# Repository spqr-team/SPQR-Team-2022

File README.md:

# SPQR-Team-2022
SPQR team soccer repo

Soccer lightweight SPQR team

On the road for Bangkok

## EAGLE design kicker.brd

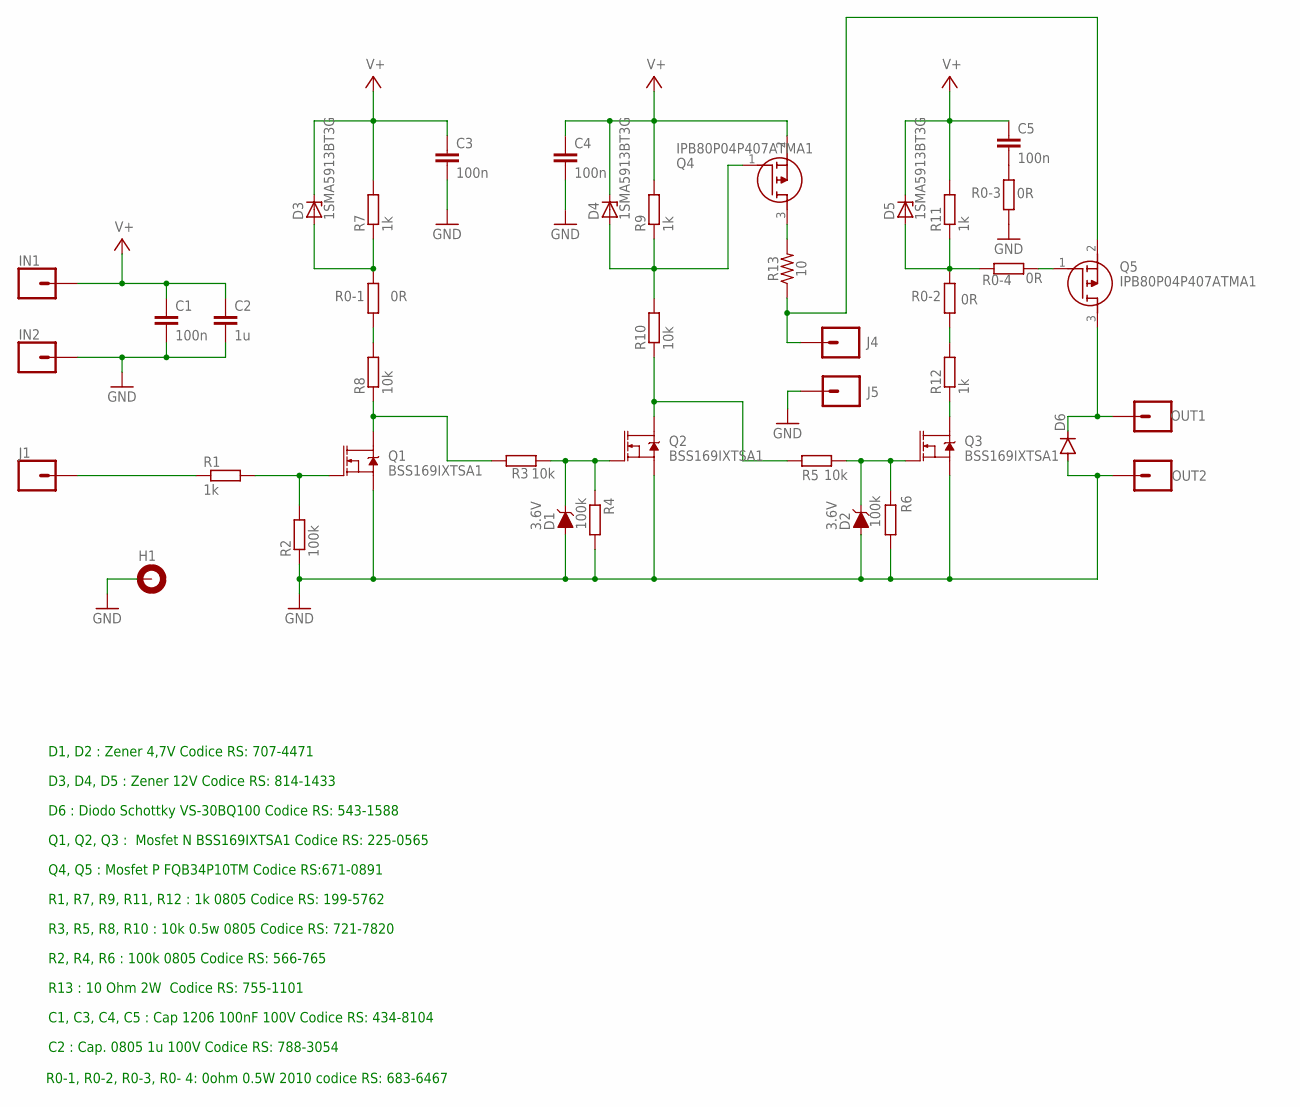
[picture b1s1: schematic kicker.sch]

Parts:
C1, C3, C4, C5: 100n; C1206
C2: 1u; C1206
D1, D2: 3.6V; SOD-323
D3, D4, D5: 1SMA5913BT3G; DO214AC
D6: DIODE-SMC; SMC
H1: MOUNT-PAD-ROUND3.0; 3,0-PAD
IN1, IN2: CONN_01; 1X01
J1, J4, J5: CONN_01; 1X01
OUT1, OUT2: CONN_01; 1X01
Q1, Q2, Q3: BSS169IXTSA1; SOT23-3
Q4, Q5: IPB80P04P407ATMA1; PG-TO263-3-2_1
R0-1, R0-2, R0-3, R0-4: 0R; R2010
R1, R7, R9, R11, R12: 1k; R1206
R2, R4, R6: 100k; R1206
R3, R5, R8, R10: 10k; R1206
R13: 10; 1210

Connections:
GND: C1.2, C2.2, C3.2, C4.2, D1.A, D2.A, D6.A, H1.B3,0, IN2.1, J5.1, OUT2.1, Q1.2 (S), Q2.2 (S), Q3.2 (S), R0-3.1, R2.1, R4.2, R6.1
unnamed: J1.1, R1.1
unnamed: Q1.1 (G), R1.2, R2.2
unnamed: D1.C, Q2.1 (G), R3.1, R4.1
unnamed: D2.C, Q3.1 (G), R5.2, R6.2
unnamed: Q1.3 (D), R3.2, R8.1
unnamed: R0-1.1, R8.2
unnamed: Q2.3 (D), R5.1, R10.1
unnamed: D4.A, Q4.1 (G), R9.1, R10.2
unnamed: Q4.3 (D), R13.2
unnamed: D3.A, R0-1.2, R7.1
unnamed: D6.C, OUT1.1, Q5.3 (D)
unnamed: J4.1, Q5.2 (S), R13.1
unnamed: R0-2.1, R12.2
unnamed: C5.2, R0-3.2
unnamed: D5.A, R0-2.2, R0-4.2, R11.1
unnamed: Q3.3 (D), R12.1
unnamed: Q5.1 (G), R0-4.1
V+: C1.1, C2.1, C3.1, C4.1, C5.1, D3.C, D4.C, D5.C, IN1.1, Q4.2 (S), R7.2, R9.2, R11.2

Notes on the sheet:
D1, D2 : Zener 4,7V Codice RS: 707-4471
D3, D4, D5 : Zener 12V Codice RS: 814-1433
R13 : 10 Ohm 2W Codice RS: 755-1101
D6 : Diodo Schottky VS-30BQ100 Codice RS: 543-1588
Q1, Q2, Q3 : Mosfet N BSS169IXTSA1 Codice RS: 225-0565
Q4, Q5 : Mosfet P FQB34P10TM Codice RS:671-0891
R1, R7, R9, R11, R12 : 1k 0805 Codice RS: 199-5762
R3, R5, R8, R10 : 10k 0.5w 0805 Codice RS: 721-7820
R2, R4, R6 : 100k 0805 Codice RS: 566-765
C1, C3, C4, C5 : Cap 1206 100nF 100V Codice RS: 434-8104
C2 : Cap. 0805 1u 100V Codice RS: 788-3054
R0-1, R0-2, R0-3, R0- 4: 0ohm 0.5W 2010 codice RS: 683-6467

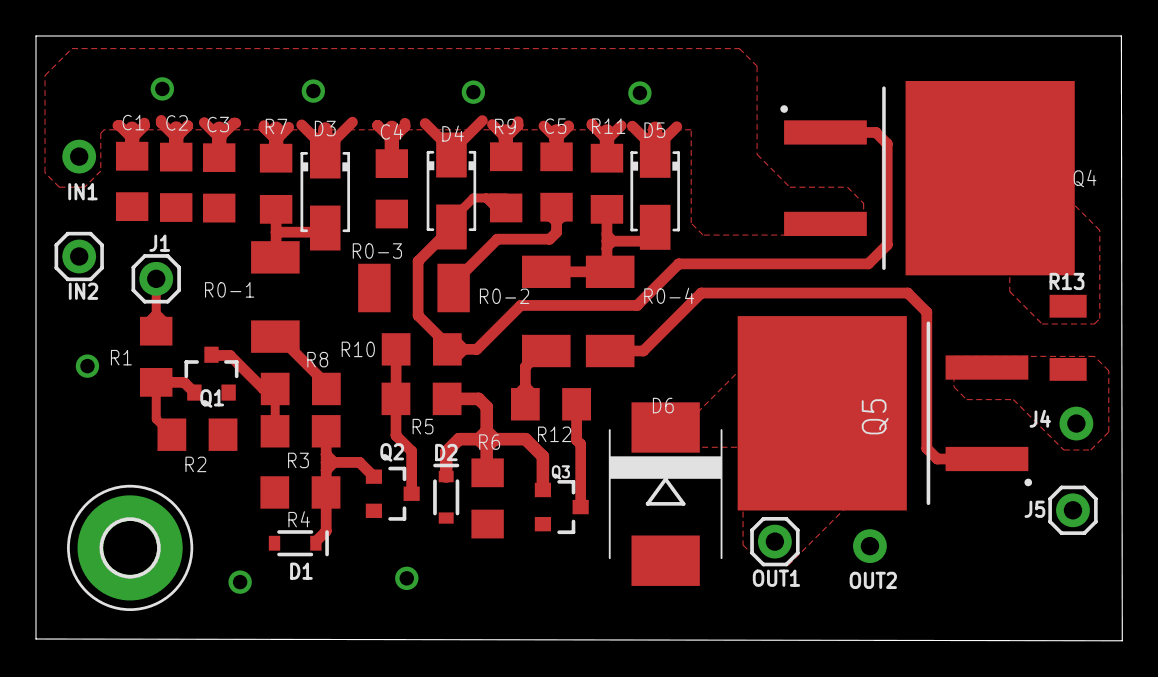
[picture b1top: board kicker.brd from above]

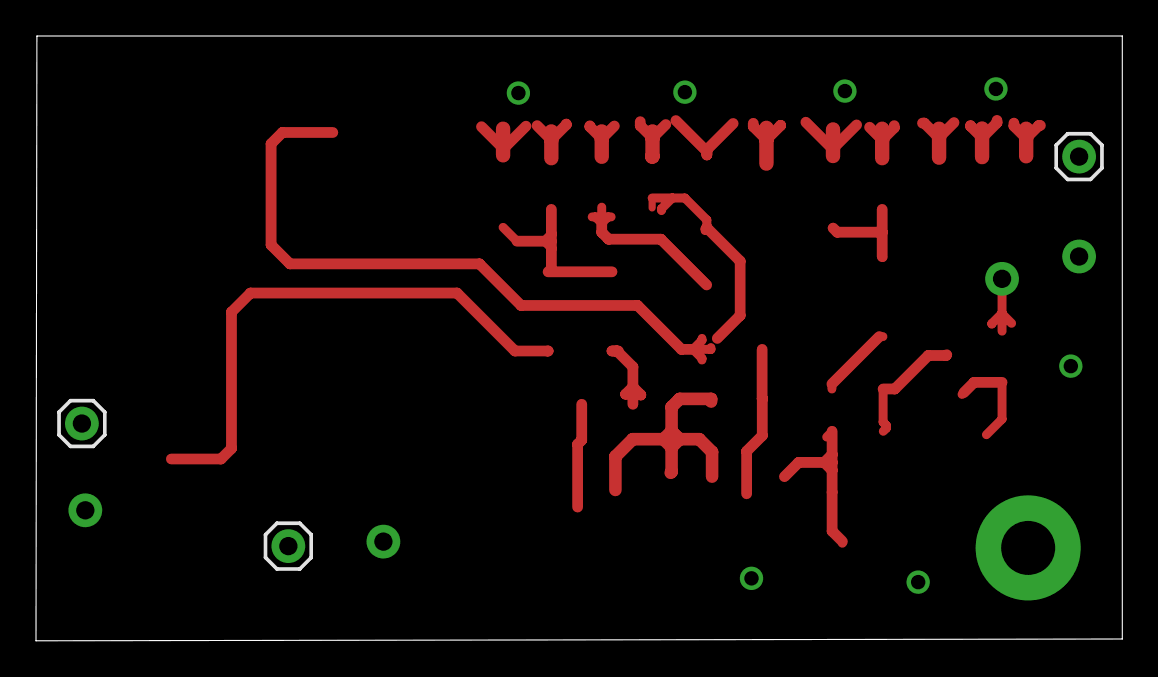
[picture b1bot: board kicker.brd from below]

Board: 2 copper layers, 60.4 x 33.6 mm, 41 parts (3 on the bottom side), 19 nets.

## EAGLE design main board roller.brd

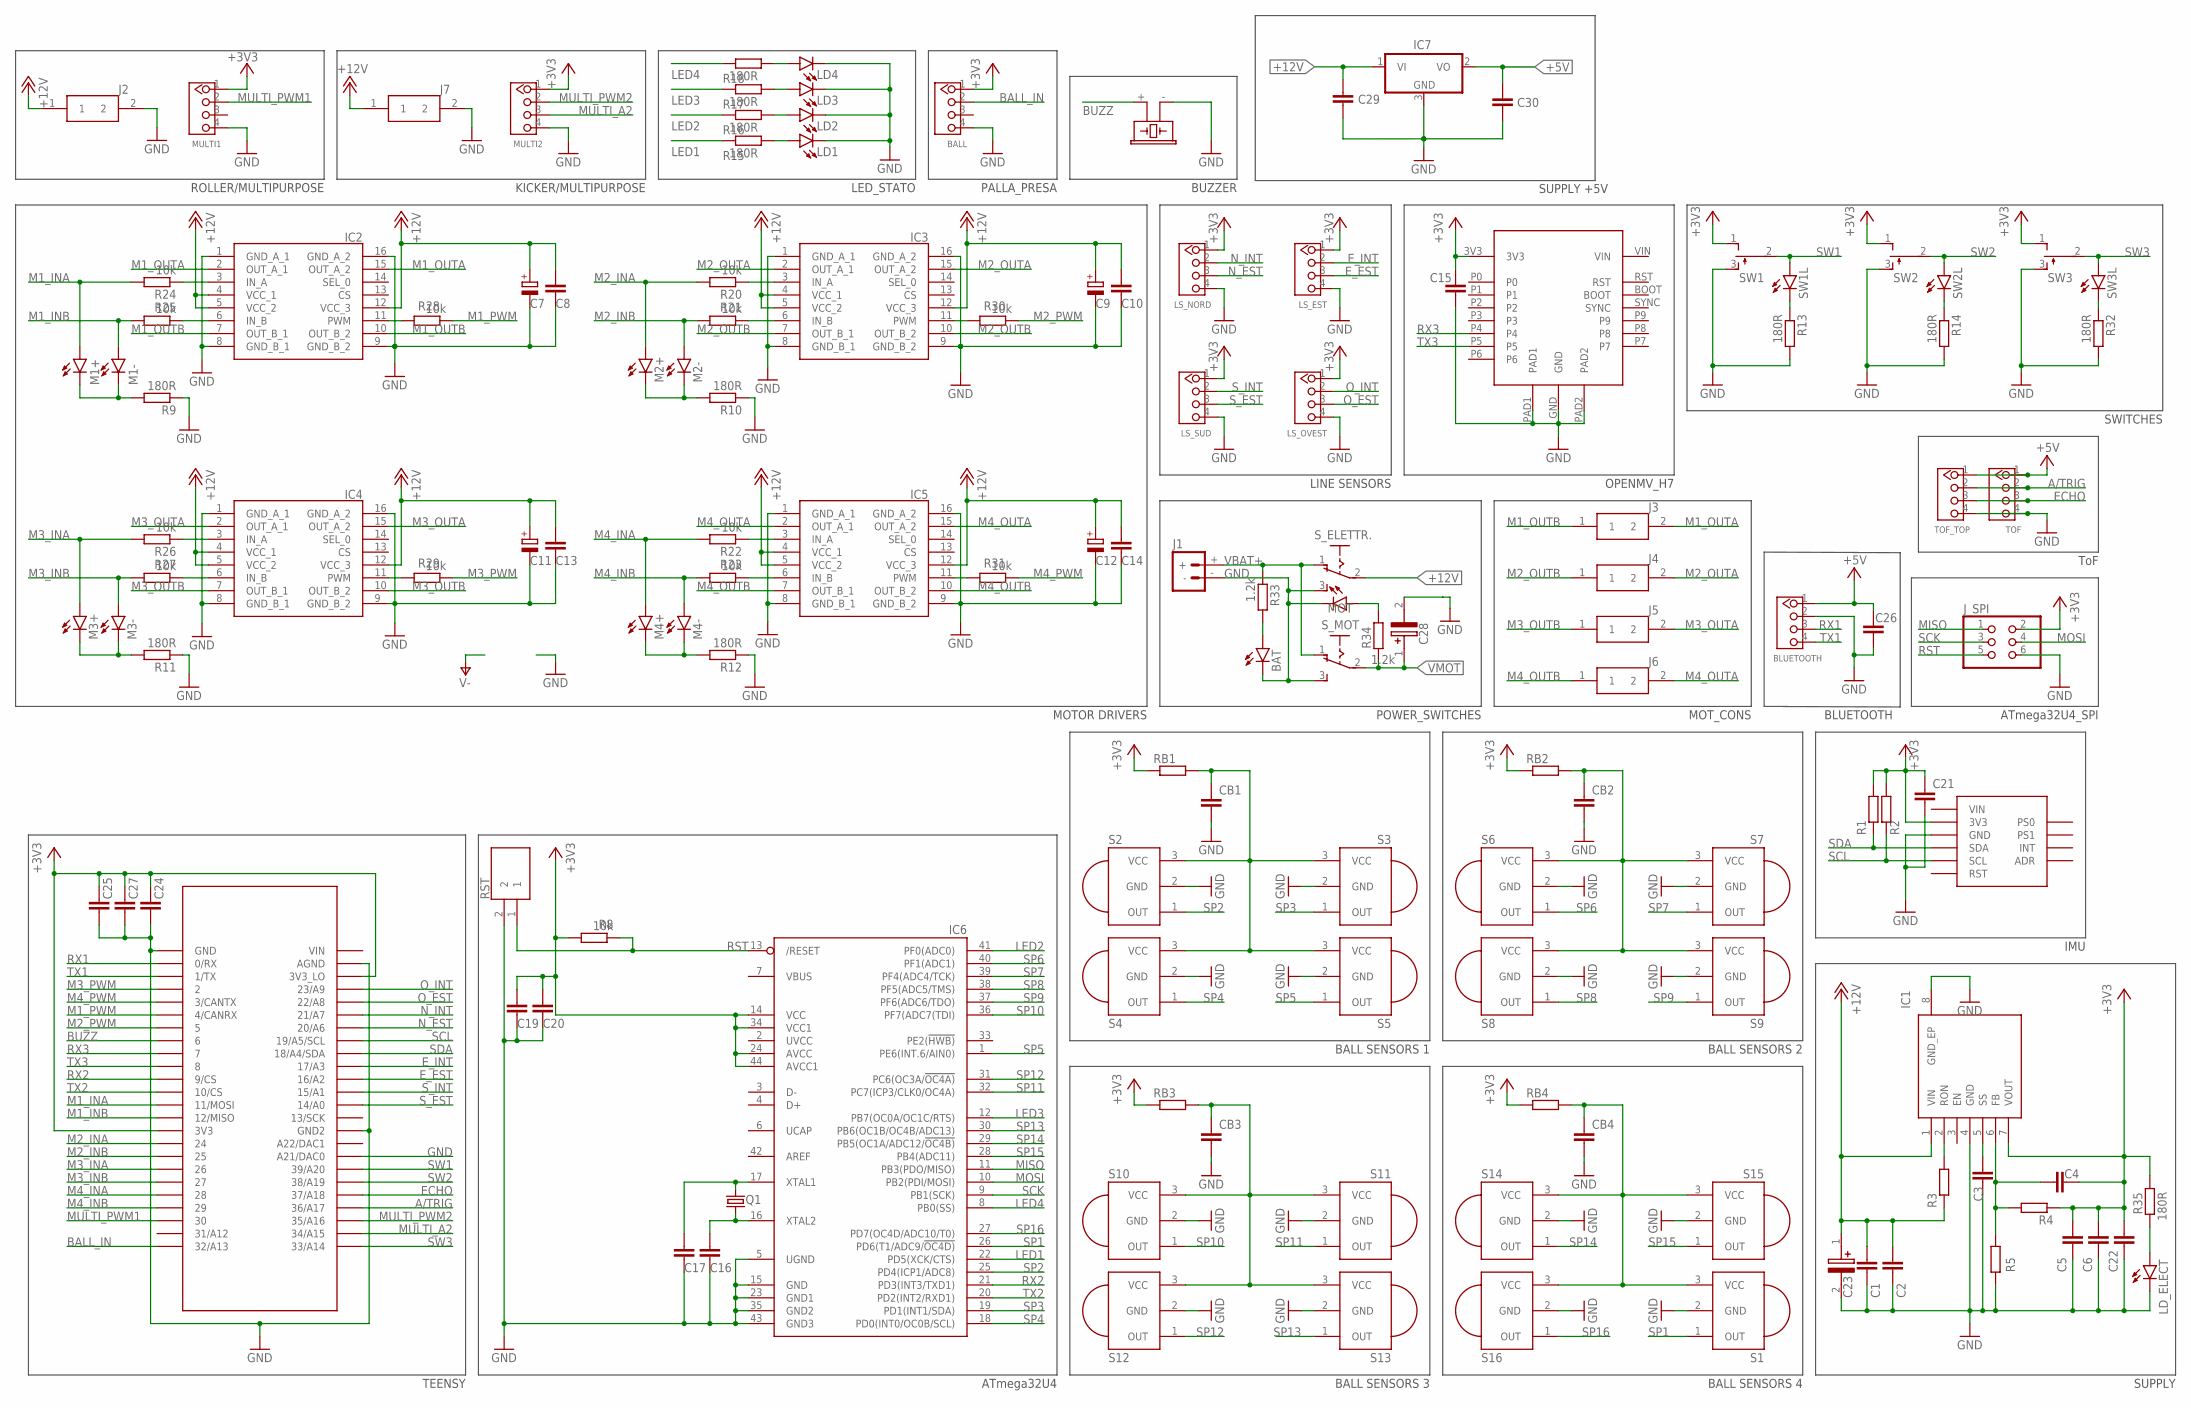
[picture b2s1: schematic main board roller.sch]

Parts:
BALL: TWIG_2.0; 2.0_1X4
BAT: LEDCHIPLED_1206; CHIPLED_1206
BLUETOOTH: TWIG_2.0; 2.0_1X4
BUZZER: F/CM12P
C1, C2, C22, C24, C27: 100n; C0805
C3, C4: 22n; C0805
C5, C6: 100u; C1206
C7: 1OOu; PANASONIC_E
C8, C10, C13, C14, C15, C20, C21, C26: 1u; C0805
C9, C11, C12: 100u; PANASONIC_E
C16, C17: 22pF; C0805
C19: 1u; C1206
C23, C28: EEV-FK1C152Q; FKV(H13)
C25: 100n; C1206
C29, C30: 1uF; C0805
CB1, CB2, CB3, CB4: 0.1uF; C0805
IC1: LMZ14202TZE-ADJ_NOPB; NDW0007A
IC2, IC3, IC4, IC5: VNH7070ASTR; SOIC127P600X175-16N
IC6: ATMEGA32U4-AU; TQFP44
IC7: 7805DT; TO252
J1: BATTERY_CONN_DEANS; DEANS
J2, J3, J4, J5, J6, J7: 43650-0201; 43650-0200
J_SPI: PINHD-2X3; 2X03
LD1, LD2, LD3, LD4: LEDCHIPLED_1206; CHIPLED_1206
LD_ELECT: LEDCHIPLED_1206; CHIPLED_1206
LS_EST: TWIG_2.0; 2.0_1X4
LS_NORD: TWIG_2.0; 2.0_1X4
LS_OVEST: TWIG_2.0; 2.0_1X4
LS_SUD: TWIG_2.0; 2.0_1X4
M1+, M1-, M2+, M2-, M3+, M3-, M4+, M4-: LEDCHIPLED_1206; CHIPLED_1206
MOT: LEDCHIPLED_1206; CHIPLED_1206
MULTI1, MULTI2: TWIG_2.0; 2.0_1X4
Q1: CRYSTALHC49UP; HC49UP
R1, R2, R8, R20, R21, R22, R23, R24, R25, R26, R27, R28, R29, R30, R31: 10k; R0805
R3: 61,9k; R0805
R4: 3,32k; R0805
R5: 1,07k; R0805
R9, R10, R11, R12, R13, R14, R15, R16, R17, R18, R32, R35: 180R; R0805
R33, R34: 1.2k; R0805
RB1, RB2, RB3, RB4: 22; R0805
RST: KSR231GLFS; KSR
S1, S2, S3, S4, S5, S6, S7, S8, S9, S10, S11, S12, S13, S14, S15, S16: PNA460XM
SW1, SW2, SW3: TL38PO; TL3XPO
SW1L, SW2L, SW3L: LEDCHIPLED_1206; CHIPLED_1206
S_ELETTR.: 255SB
S_MOT: 255SB
TOF: TWIG_2.0; 2.0_1X4
TOF_TOP: TWIG_2.0; 2.0_1X4
U$1: TEENSY_3.5/3.6
U$2: OPENMV_H7
U$4: BNO055

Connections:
+3V3: BALL.1, C4.2, C5.1, C6.1, C15.1, C19.1, C20.1, C21.1, C22.1, C24.1, C25.1, C27.1, IC1.7 (VOUT), IC6.14 (VCC), IC6.24 (AVCC), IC6.34 (VCC1), IC6.44 (AVCC1), J_SPI.2, LS_EST.1, LS_NORD.1, LS_OVEST.1, LS_SUD.1, MULTI1.1, MULTI2.1, R1.2, R2.2, R4.1, R8.2, R35.2, RB1.1, RB2.1, RB3.1, RB4.1, SW1.1 (O), SW2.1 (O), SW3.1 (O), U$1.3V3, U$1.3V3_LO, U$2.3V3, U$4.3V3
+5V: BLUETOOTH.1, C26.1, C30.1, IC7.2 (VO), TOF.1, TOF_TOP.1
+12V: C1.1, C2.1, C23.1 (+), C29.1, IC1.1 (VIN), IC7.1 (VI), J2.1, J7.1, R3.1, S_ELETTR..2
A/TRIG: TOF.2, TOF_TOP.2, U$1.36/A17
BALL_IN: BALL.2, U$1.32/A13
BUZZ: BUZZER.+ (1), U$1.6
ECHO: TOF.3, TOF_TOP.3, U$1.37/A18
E_EST: LS_EST.3, U$1.16/A2
E_INT: LS_EST.2, U$1.17/A3
GND: BALL.4, BAT.C, BLUETOOTH.2, BUZZER.- (2), C1.2, C2.2, C3.2, C5.2, C6.2, C7.-, C8.2, C9.-, C10.2, C11.-, C12.-, C13.2, C14.2, C15.2, C16.2, C17.2, C19.2, C20.2, C21.2, C22.2, C23.2 (-), C24.2, C25.2, C26.2, C27.2, C28.2 (-), C29.2, C30.2, CB1.2, CB2.2, CB3.2, CB4.2, IC1.4 (GND), IC1.8 (GND_EP), IC2.1 (GND_A_1), IC2.8 (GND_B_1), IC2.9 (GND_B_2), IC2.16 (GND_A_2), IC3.1 (GND_A_1), IC3.8 (GND_B_1), IC3.9 (GND_B_2), IC3.16 (GND_A_2), IC4.1 (GND_A_1), IC4.8 (GND_B_1), IC4.9 (GND_B_2), IC4.16 (GND_A_2), IC5.1 (GND_A_1), IC5.8 (GND_B_1), IC5.9 (GND_B_2), IC5.16 (GND_A_2), IC6.5 (UGND), IC6.15 (GND), IC6.23 (GND1), IC6.35 (GND2), IC6.43 (GND3), IC7.3 (GND), J1.-, J2.2, J7.2, J_SPI.6, LD1.C, LD2.C, LD3.C, LD4.C, LD_ELECT.C, LS_EST.4, LS_NORD.4, LS_OVEST.4, LS_SUD.4, MOT.C, MULTI1.4, MULTI2.4, R5.1, R9.1, R10.1, R11.1, R12.1, R13.2, R14.2, R32.2, RST.2, S1.2 (GND), S2.2 (GND), S3.2 (GND), S4.2 (GND), S5.2 (GND), S6.2 (GND), S7.2 (GND), S8.2 (GND), S9.2 (GND), S10.2 (GND), S11.2 (GND), S12.2 (GND), S13.2 (GND), S14.2 (GND), S15.2 (GND), S16.2 (GND), SW1.3 (S), SW2.3 (S), SW3.3 (S), S_ELETTR..3 (S), S_MOT.3 (S), TOF.4, TOF_TOP.4, U$1.21/DAC0 (A21/DAC0), U$1.AGND, U$1.GND, U$1.GND2, U$2.GND, U$2.PAD1, U$2.PAD2, U$4.GND
INA_1: IC2.3 (IN_A), R24.1
INA_2: IC3.3 (IN_A), R20.1
INA_3: IC4.3 (IN_A), R26.1
INA_4: IC5.3 (IN_A), R22.1
INB_1: IC2.6 (IN_B), R25.1
INB_2: IC3.6 (IN_B), R21.1
INB_3: IC4.6 (IN_B), R27.1
INB_4: IC5.6 (IN_B), R23.1
LED1: IC6.22 (PD5(XCK/CTS)), R15.1
LED2: IC6.41 (PF0(ADC0)), R16.1
LED3: IC6.12 (PB7(OC0A/OC1C/RTS)), R17.1
LED4: IC6.8 (PB0(SS)), R18.1
M1_INA: M1+.A, R24.2, U$1.11/MOSI
M1_INB: M1-.A, R25.2, U$1.12/MISO
M1_OUTA: IC2.2 (OUT_A_1), IC2.15 (OUT_A_2), J3.2
M1_OUTB: IC2.7 (OUT_B_1), IC2.10 (OUT_B_2), J3.1
M1_PWM: R28.1, U$1.4/CANRX
M2_INA: M2+.A, R20.2, U$1.24
M2_INB: M2-.A, R21.2, U$1.25
M2_OUTA: IC3.2 (OUT_A_1), IC3.15 (OUT_A_2), J4.2
M2_OUTB: IC3.7 (OUT_B_1), IC3.10 (OUT_B_2), J4.1
M2_PWM: R30.1, U$1.5
M3_INA: M3+.A, R26.2, U$1.26
M3_INB: M3-.A, R27.2, U$1.27
M3_OUTA: IC4.2 (OUT_A_1), IC4.15 (OUT_A_2), J5.2
M3_OUTB: IC4.7 (OUT_B_1), IC4.10 (OUT_B_2), J5.1
M3_PWM: R29.1, U$1.2
M4_INA: M4+.A, R22.2, U$1.28
M4_INB: M4-.A, R23.2, U$1.29
M4_OUTA: IC5.2 (OUT_A_1), IC5.15 (OUT_A_2), J6.2
M4_OUTB: IC5.7 (OUT_B_1), IC5.10 (OUT_B_2), J6.1
M4_PWM: R31.1, U$1.3/CANTX
MISO: IC6.11 (PB3(PDO/MISO)), J_SPI.1
MOSI: IC6.10 (PB2(PDI/MOSI)), J_SPI.4
MULTI_A2: MULTI2.3, U$1.34/A15
MULTI_PWM1: MULTI1.2, U$1.30
MULTI_PWM2: MULTI2.2, U$1.35/A16
unnamed: IC1.2 (RON), R3.2
unnamed: C4.1, IC1.6 (FB), R4.2, R5.2
unnamed: C3.1, IC1.5 (SS)
unnamed: LD4.A, R18.2
unnamed: C17.1, IC6.17 (XTAL1), Q1.2
unnamed: C16.1, IC6.16 (XTAL2), Q1.1
unnamed: M2+.C, M2-.C, R10.2
unnamed: M1+.C, M1-.C, R9.2
unnamed: M3+.C, M3-.C, R11.2
unnamed: M4+.C, M4-.C, R12.2
unnamed: R13.1, SW1L.C
unnamed: R14.1, SW2L.C
unnamed: R32.1, SW3L.C
unnamed: LD1.A, R15.2
unnamed: LD2.A, R16.2
unnamed: LD3.A, R17.2
unnamed: BAT.A, R33.2
unnamed: MOT.A, R34.2
unnamed: LD_ELECT.A, R35.1
N_EST: LS_NORD.3, U$1.20/A6
N_INT: LS_NORD.2, U$1.21/A7
O_EST: LS_OVEST.3, U$1.22/A8
O_INT: LS_OVEST.2, U$1.23/A9
POWER_BLOCK_1: CB1.1, RB1.2, S2.3 (VCC), S3.3 (VCC), S4.3 (VCC), S5.3 (VCC)
POWER_BLOCK_2: CB2.1, RB2.2, S6.3 (VCC), S7.3 (VCC), S8.3 (VCC), S9.3 (VCC)
POWER_BLOCK_3: CB3.1, RB3.2, S10.3 (VCC), S11.3 (VCC), S12.3 (VCC), S13.3 (VCC)
POWER_BLOCK_4: CB4.1, RB4.2, S1.3 (VCC), S14.3 (VCC), S15.3 (VCC), S16.3 (VCC)
PWM3: IC4.11 (PWM), R29.2
PWM_1: IC2.11 (PWM), R28.2
PWM_2: IC3.11 (PWM), R30.2
PWM_4: IC5.11 (PWM), R31.2
RST: IC6.13 (/RESET), J_SPI.5, R8.1, RST.1
RX1: BLUETOOTH.3, U$1.0/RX
RX2: IC6.21 (PD3(INT3/TXD1)), U$1.9/CS
RX3: U$1.7, U$2.P4
SCK: IC6.9 (PB1(SCK)), J_SPI.3
SCL: R2.1, U$1.19/A5/SCL, U$4.SCL
SDA: R1.1, U$1.18/A4/SDA, U$4.SDA
SP1: IC6.26 (PD6(T1/ADC9/!OC4D)), S1.1 (OUT)
SP2: IC6.25 (PD4(ICP1/ADC8)), S2.1 (OUT)
SP3: IC6.19 (PD1(INT1/SDA)), S3.1 (OUT)
SP4: IC6.18 (PD0(INT0/OC0B/SCL)), S4.1 (OUT)
SP5: IC6.1 (PE6(INT.6/AIN0)), S5.1 (OUT)
SP6: IC6.40 (PF1(ADC1)), S6.1 (OUT)
SP7: IC6.39 (PF4(ADC4/TCK)), S7.1 (OUT)
SP8: IC6.38 (PF5(ADC5/TMS)), S8.1 (OUT)
SP9: IC6.37 (PF6(ADC6/TDO)), S9.1 (OUT)
SP10: IC6.36 (PF7(ADC7(TDI)), S10.1 (OUT)
SP11: IC6.32 (PC7(ICP3/CLK0/OC4A)), S11.1 (OUT)
SP12: IC6.31 (PC6(OC3A/!OC4A)), S12.1 (OUT)
SP13: IC6.30 (PB6(OC1B/OC4B/ADC13)), S13.1 (OUT)
SP14: IC6.29 (PB5(OC1A/ADC12/!OC4B)), S14.1 (OUT)
SP15: IC6.28 (PB4(ADC11)), S15.1 (OUT)
SP16: IC6.27 (PD7(OC4D/ADC10/T0)), S16.1 (OUT)
SW1: SW1.2, SW1L.A, U$1.39/A20
SW2: SW2.2, SW2L.A, U$1.38/A19
SW3: SW3.2, SW3L.A, U$1.33/A14
S_EST: LS_SUD.3, U$1.14/A0
S_INT: LS_SUD.2, U$1.15/A1
TX1: BLUETOOTH.4, U$1.1/TX
TX2: IC6.20 (PD2(INT2/RXD1)), U$1.10/CS
TX3: U$1.8, U$2.P5
VBAT+: J1.+, R33.1, S_ELETTR..1 (O), S_MOT.1 (O)
VMOT: C7.+, C8.1, C9.+, C10.1, C11.+, C12.+, C13.1, C14.1, C28.1 (+), IC2.4 (VCC_1), IC2.5 (VCC_2), IC2.12 (VCC_3), IC3.4 (VCC_1), IC3.5 (VCC_2), IC3.12 (VCC_3), IC4.4 (VCC_1), IC4.5 (VCC_2), IC4.12 (VCC_3), IC5.4 (VCC_1), IC5.5 (VCC_2), IC5.12 (VCC_3), R34.1, S_MOT.2

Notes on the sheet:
TEENSY
IMU
SUPPLY
POWER_SWITCHES
BALL SENSORS 1
BALL SENSORS 2
BALL SENSORS 3
BALL SENSORS 4
LINE SENSORS
MOTOR DRIVERS
OPENMV_H7
ATmega32U4
ATmega32U4_SPI
SWITCHES
BUZZER
LED_STATO
MOT_CONS
BLUETOOTH
ToF
ROLLER/MULTIPURPOSE
KICKER/MULTIPURPOSE
PALLA_PRESA
SUPPLY +5V

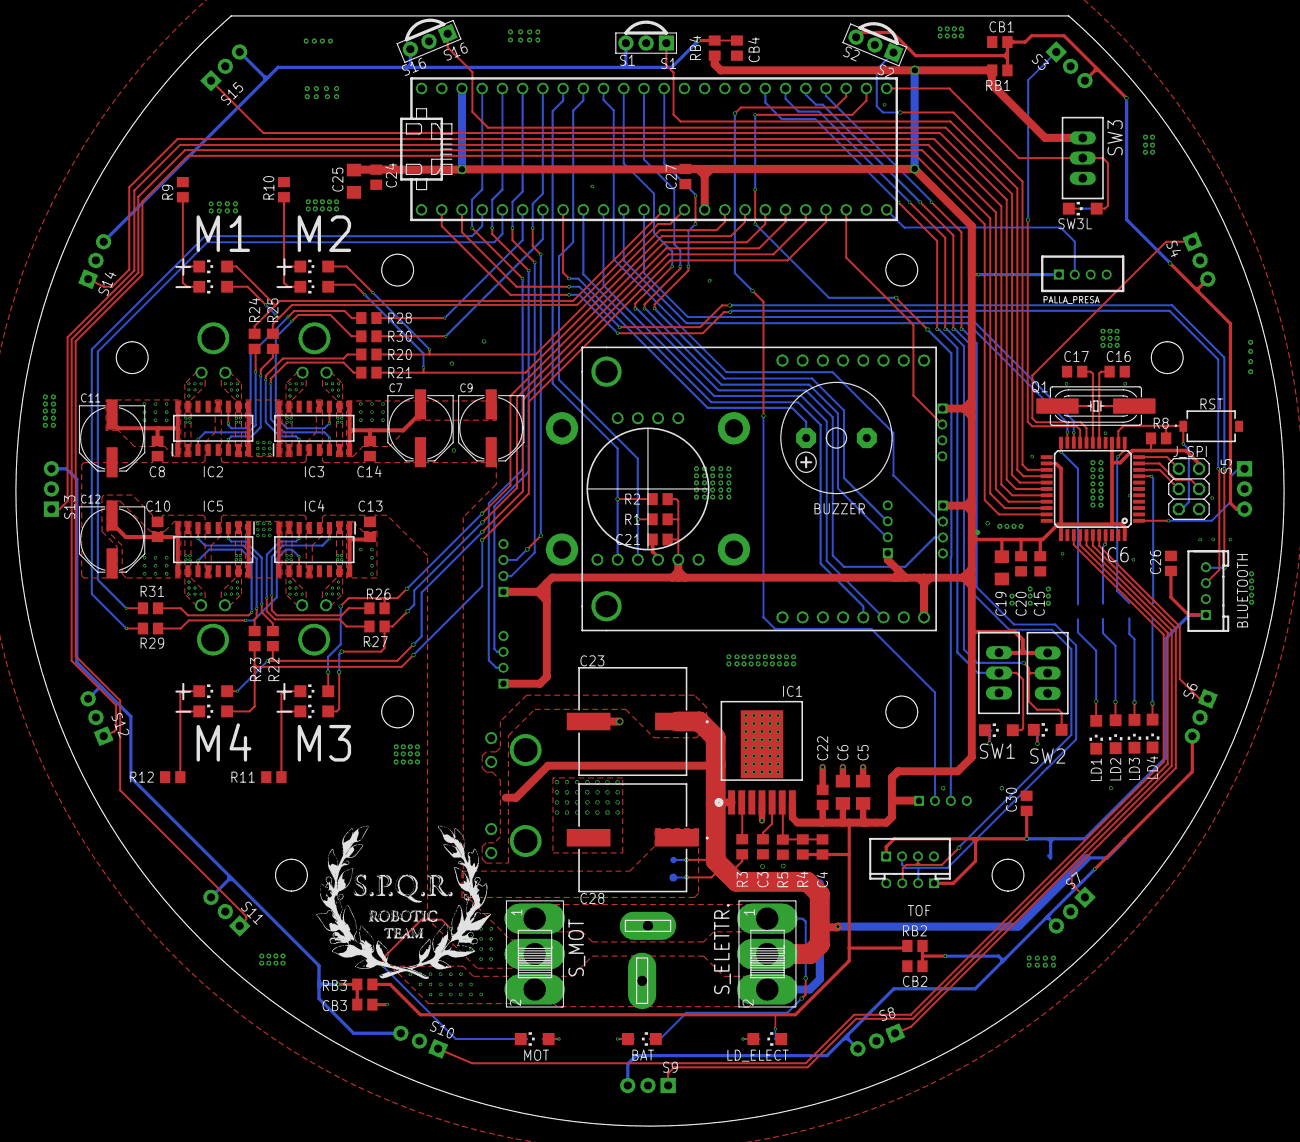
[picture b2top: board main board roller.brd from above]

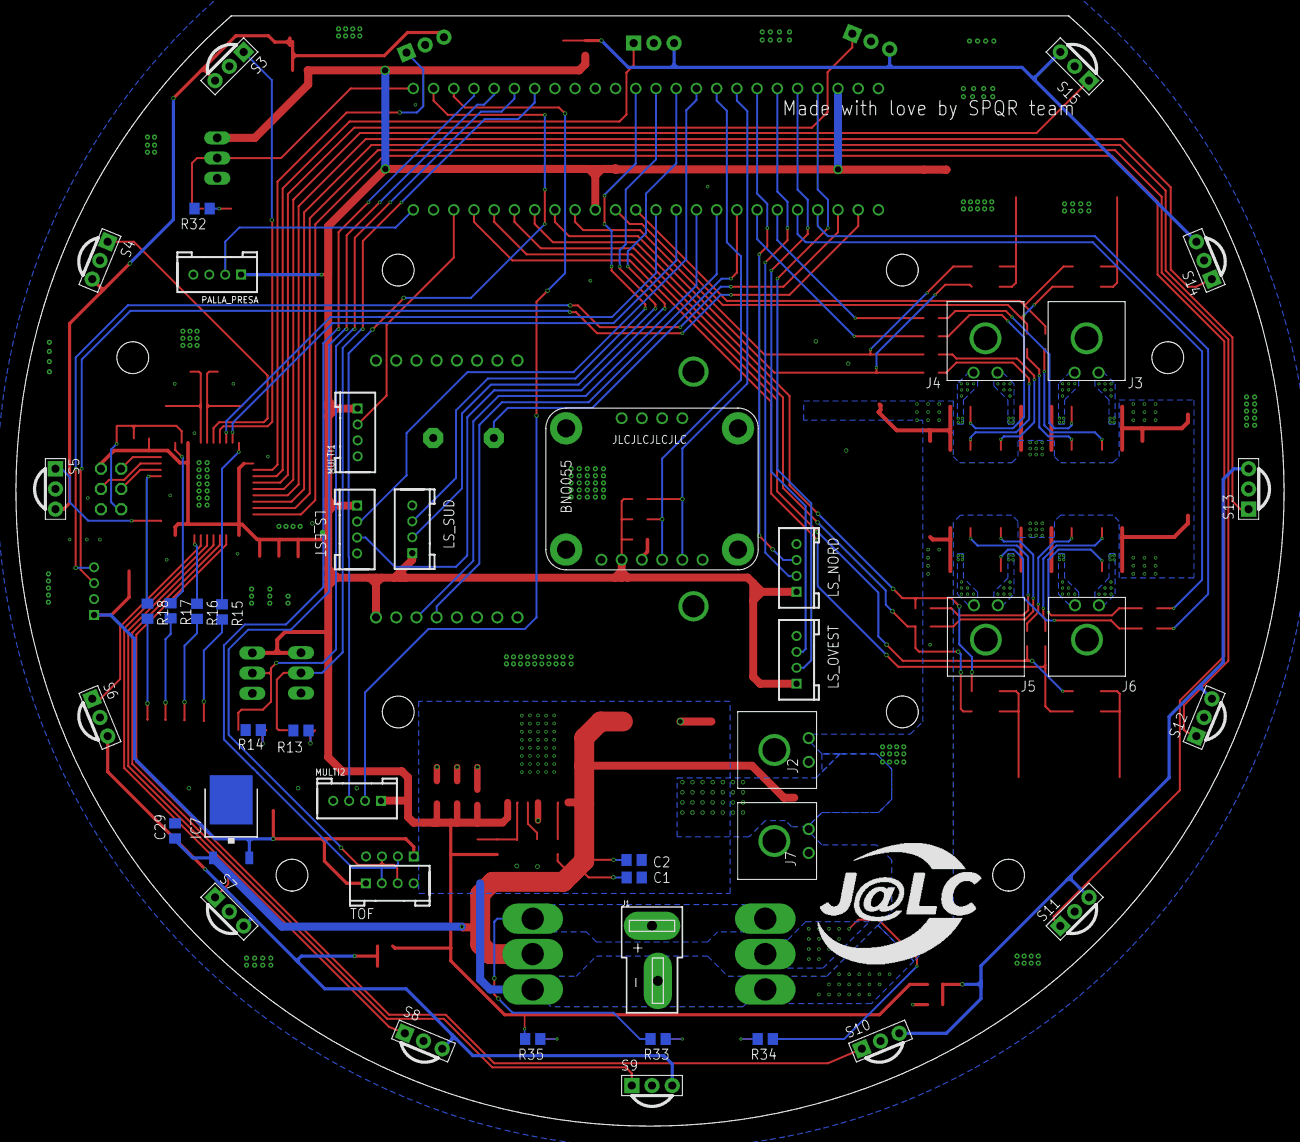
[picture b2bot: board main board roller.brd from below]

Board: 2 copper layers, 159.3 x 139.4 mm, 139 parts (43 on the bottom side), 111 nets.

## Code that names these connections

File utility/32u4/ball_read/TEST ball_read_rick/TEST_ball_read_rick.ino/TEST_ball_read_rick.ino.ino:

// ball read 32u4
// test valori letti dai sensori 

/**
  sensorNumber Mapping
    sensorNumber  Angle Pin Port
    S1      0     26  PD6
    S2            25  PD4
    S3            19  PD1
    S4            18  PD0
    S5      90    1   PE6
    S6            40  PF1
    S7            39  PF4
    S8            38  PF5
    S9      180   37  PF6
    S10           36  PF7
    S11           32  PC7
    S12           31  PC6
    S13     270   30  PB6
    S14           29  PB5
    S15           28  PB4
    S16           27  PD7
    loop cycle duration: 3.2 millis
**/


// reading sensorNumbers faster by PORT register
#define S5 ((PINE & 64 ) >> 6)

#define S11 ((PINC & 128 ) >> 7)
#define S12 ((PINC & 64 ) >> 6)

#define S13 ((PINB & 64 ) >> 6)
#define S14 ((PINB & 32 ) >> 5)
#define S15 ((PINB & 16) >> 4)

#define S1 ((PIND & 64 ) >> 6)
#define S2 ((PIND & 16 ) >> 4)
#define S3 ((PIND & 2 ) >> 1)
#define S4 (PIND & 1 )
#define S16 ((PIND & 128) >> 7)

#define S6 ((PINF & 2 ) >> 1)
#define S7 ((PINF & 16 ) >> 4)
#define S8 ((PINF & 32 ) >> 5)
#define S9 ((PINF & 64 ) >> 6)
#define S10 ((PINF & 128 ) >> 7)


#define NCYCLES  250    // number of readings (MAX = 255)
#define TOO_HIGH 230    // TOO_HIGH values
#define TOO_LOW   45    // TOO_LOW  values

// init LEDS
#define LED1ON (PORTD = PORTD | 0b00100000)
#define LED1OFF (PORTD = PORTD & 0b11011111)

#define LED2ON (PORTF = PORTF | 0b00000001)
#define LED2OFF (PORTF = PORTF & 0b11111110)

#define LED3ON (PORTB = PORTB | 0b10000000)
#define LED3OFF (PORTB = PORTB & 0b01111111)

#define LED4ON (PORTB = PORTB | 0b00000001)
#define LED4OFF (PORTB = PORTB & 0b11111110)


byte counter[16];
byte distance;
byte maxCounter = 0;
byte sensorNumber = 0;

unsigned long sendtimer = 0;

float angle; 
float xs[16];
float ys[16];


void setup() {
  delay(1000);

  // init serial ATmega32u4-teensy
  Serial1.begin(57600);

  //For now replace pinMode with writes to the direction register. 
  //We don't know if pinMode will work on those sensorNumbers, and it has proven not be working on digitalWrite for reasons probably relative to compatibility between Arduino and our board,
  //but this needs further investigation*/  
  //Set the LEDs as outputs, keep the rest as input by default

  //LED3(PB7) and LED4 (PB0)
  DDRB |= 0b10000001;
  //LED2 (PF0)
  DDRF |= 0b00000001;
  //LED1 (PD5)
  DDRD |= 0b00100000;
  
  /*pinMode(26, INPUT);   //S1
  pinMode(25, INPUT);   //S2
  pinMode(19, INPUT);   //S3
  pinMode(18, INPUT);   //S4
  pinMode(1, INPUT);    //S5
  pinMode(40, INPUT);   //S6
  pinMode(39, INPUT);   //S7
  pinMode(38, INPUT);   //S8
  pinMode(37, INPUT);   //S9
  pinMode(36, INPUT);   //S10
  pinMode(32, INPUT);   //S11
  pinMode(31, INPUT);   //S12
  pinMode(30, INPUT);   //S13
  pinMode(29, INPUT);   //S14
  pinMode(28, INPUT);   //S15
  pinMode(27, INPUT);   //S16*/
  
  for (int i = 0; i < 16; i++) {
    xs[i] = cos((22.5 * PI / 180) * i);
    ys[i] = sin((22.5 * PI / 180) * i);
  }
}



void loop() { 
  
  // reset counters
  for (byte i = 0; i < 16; i++) {
    counter[i] = 0;
  }

  //reads ball sensors from registers 
  for (byte i = 0; i < NCYCLES; i++) {
    counter[0] += !S1;
    counter[1] += !S2;
    counter[2] += !S3;
    counter[3] += !S4;
    counter[4] += !S5;
    counter[5] += !S6;
    counter[6] += !S7;
    counter[7] += !S8;
    counter[8] += !S9;
    counter[9] += !S10;
    counter[10] += !S11;
    counter[11] += !S12;
    counter[12] += !S13;
    counter[13] += !S14;
    counter[14] += !S15;
    counter[15] += !S16;
  }
  

  // invio valori sensori 
  for(byte i = 0; i < NCYCLES; i++) {
    Serial1.println("===========");
    Serial1.println("S1: " + String(counter[0]));
    Serial1.println("S2: " + String(counter[1]));
    Serial1.println("S3: " + String(counter[2]));
    Serial1.println("S4: " + String(counter[3]));
    Serial1.println("S5: " + String(counter[4]));
    Serial1.println("S6: " + String(counter[5]));
    Serial1.println("S7: " + String(counter[6]));
    Serial1.println("S8: " + String(counter[7]));
    Serial1.println("S9: " + String(counter[8]));
    Serial1.println("S10: " + String(counter[9]));
    Serial1.println("S11: " + String(counter[10]));
    Serial1.println("S12: " + String(counter[11]));
    Serial1.println("S13: " + String(counter[12]));
    Serial1.println("S14: " + String(counter[13]));
    Serial1.println("S15: " + String(counter[14]));
    Serial1.println("S16: " + String(counter[15]));
    Serial1.println("-----------");
  }

  delay(10);
  
}




// FUNZIONI DI EMA
/**--- READ BALL USING sensorNumberS ANGLE INTERPOLATION ---**/
/*
void readBallInterpolation() {
  
  for (byte i = 0; i < 16; i++) {
    counter[i] = 0;
  }

  //reads from the register
  for (byte i = 0; i < NCYCLES; i++) {
    counter[0] += !S1;
    counter[1] += !S2;
    counter[2] += !S3;
    counter[3] += !S4;
    counter[4] += !S5;
    counter[5] += !S6;
    counter[6] += !S7;
    counter[7] += !S8;
    counter[8] += !S9;
    counter[9] += !S10;
    counter[10] += !S11;
    counter[11] += !S12;
    counter[12] += !S13;
    counter[13] += !S14;
    counter[14] += !S15;
    counter[15] += !S16;
  }

  float x = 0, y = 0;
  maxCounter = 0;
  for (byte i = 0; i < 16; i++) {
    if (counter[i] > TOO_HIGH || counter[i] < TOO_LOW) counter[i] = 0;

    x += xs[i] * counter[i];
    y += ys[i] * counter[i];

    if (counter[i] > maxCounter) {
      maxCounter = counter[i];
      sensorNumber = i;
    }
  }

  distance = maxCounter;

  angle = atan2(y, x) * 180 / PI;
  angle = ((int)(angle + 360)) % 360;

  //distance is 0 when not seeing ball
  //dist = hypot(x, y);

  //turn led on if the robot is seeing ball
  if (distance == 0) {
    LED1OFF;
  } else {
    LED1ON;
  }
}



unsigned long sendtimer = 0;

void sendDataInterpolation() {
  //We must ensure that each number is expressed with three digits, adding leading zeros if necessary, to further improve transmission reliability
  String str_angle = String((int) angle, DEC);
  String str_distance = String(NCYCLES - (int) distance, DEC);

  String sendStr_angle = "";
  String sendStr_distance = "";

  if(str_angle.length() == 1) sendStr_angle = "00" + str_angle;
  else if(str_angle.length() == 2) sendStr_angle = "0" + str_angle;
  else sendStr_angle = str_angle;
  
  if(str_distance.length() == 1) sendStr_distance = "00" + str_distance;
  else if(str_distance.length() == 2) sendStr_distance = "0" + str_distance;
  else sendStr_distance = str_distance;

  //slow down the communciation a little bit, or it might get very messy
  if(millis() - sendtimer > 40){
    Serial1.print("b");
    Serial1.print(sendStr_angle);
    Serial1.print("-");
    Serial1.print(sendStr_distance);
    Serial1.print("IB");
    sendtimer = millis();
  }

}


void test() {
  readBallInterpolation();
  
  Serial1.println("===========");
  Serial1.print(S1);
  Serial1.print(" | ");
  Serial1.print(S2);
  Serial1.print(" | ");
  Serial1.print(S3);
  Serial1.print(" | ");
  Serial1.print(S4);
  Serial1.print(" | ");
  Serial1.print(S5);
  Serial1.print(" | ");
  Serial1.print(S6);
  Serial1.print(" | ");
  Serial1.print(S7);
  Serial1.print(" | ");
  Serial1.print(S8);
  Serial1.print(" | ");
  Serial1.print(S9);
  Serial1.print(" | ");
  Serial1.print(S10);
  Serial1.print(" | ");
  Serial1.print(S11);
  Serial1.print(" | ");
  Serial1.print(S12);
  Serial1.print(" | ");
  Serial1.print(S13);
  Serial1.print(" | ");
  Serial1.print(S14);
  Serial1.print(" | ");
  Serial1.print(S15);
  Serial1.print(" | ");
  Serial1.print(S16);
  Serial1.print(" ---  ");
  Serial1.println(sensorNumber);
  Serial1.println("===========");
  delay(100);

}


void printCounter() {
  for (int i = 0; i < 16; i++) {
    Serial1.print(counter[i]);
    Serial1.print(" | ");
  }
    Serial1.print("\t\t| Angle: " );
    Serial1.print(angle);
    Serial1.print("||| Distance: " );
    Serial1.print(distance);
    
  Serial1.println();
  delay(100);
}


void readFromTeensy(){
  while(Serial1.available()){
    byte b = Serial1.read();
    if(b & 0b00000001 == 1) LED2ON;
    else LED2OFF;
    if((b & 0b00000010) >> 1 == 1) LED3ON;
    else LED3OFF;
    if((b & 0b00000100) >> 2 == 1) LED4ON;
    else LED4OFF;
  }
}

*/

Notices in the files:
parts and their libraries:
SparkFun-DiscreteSemi: Licensing: Creative Commons ShareAlike 4.0 International - https://creativecommons.org/licenses/by-sa/4.0
